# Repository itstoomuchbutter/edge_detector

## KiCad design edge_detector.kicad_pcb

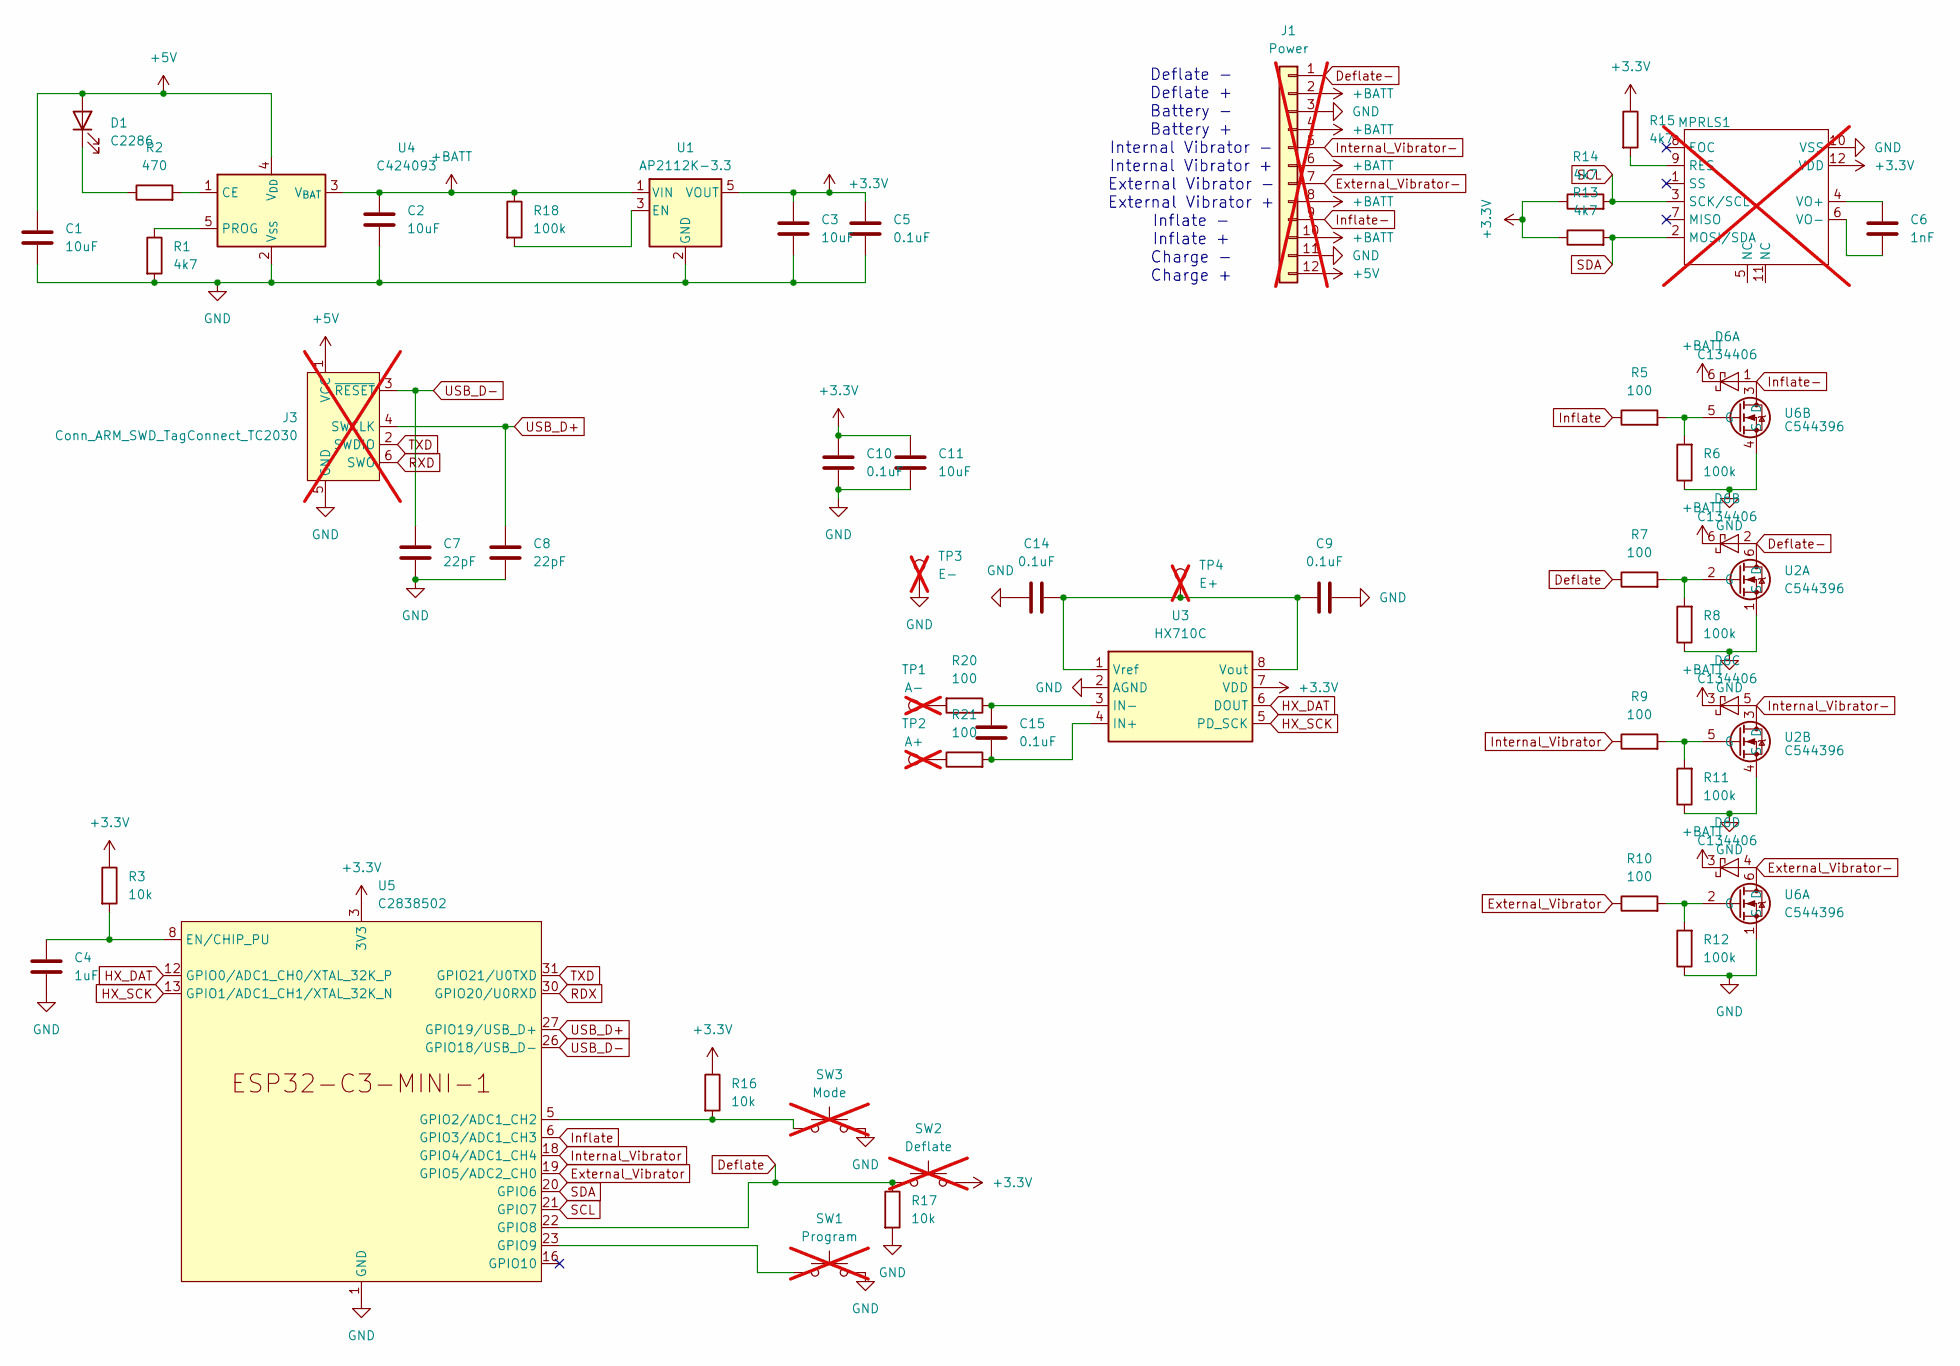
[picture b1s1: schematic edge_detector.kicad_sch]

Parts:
C1, C2, C3, C11: 10uF; C_0402_1005Metric; LCSC C15525
C4: 1uF; C_0402_1005Metric; LCSC C52923
C5, C9, C10, C14, C15: 0.1uF; C_0402_1005Metric; LCSC C1525
C6: 1nF; C_0402_1005Metric; LCSC C1523
C7, C8: 22pF; C_0402_1005Metric; LCSC C1555
D1: C2286; LED_0603_1608Metric; LCSC C2286
D6: C134406; SOT-363_SC-70-6; LCSC C134406
J1: Power; Molex_PicoBlade_53048-1210_1x12_P1.25mm_Horizontal; not fitted
J3: Conn_ARM_SWD_TagConnect_TC2030; Tag-Connect_TC2030-IDC-NL_2x03_P1.27mm_Vertical; not fitted
MPRLS1: MPRLS0015PA0000SA; not fitted
R1, R13, R14, R15: 4k7; R_0402_1005Metric; LCSC C25900
R2: 470; R_0402_1005Metric; LCSC C25117
R3, R16, R17: 10k; R_0402_1005Metric; LCSC C25744
R5, R7, R9, R10, R20, R21: 100; R_0402_1005Metric; LCSC C25076
R6, R8, R11, R12, R18: 100k; R_0402_1005Metric; LCSC C25741
SW1: Program; SW_SPST_PTS645; not fitted
SW2: Deflate; SW_SPST_PTS645; not fitted
SW3: Mode; SW_SPST_PTS645; not fitted
TP1: A-; TestPoint_Pad_1.0x1.0mm; not fitted
TP2: A+; TestPoint_Pad_1.0x1.0mm; not fitted
TP3: E-; TestPoint_Pad_1.0x1.0mm; not fitted
TP4: E+; TestPoint_Pad_1.0x1.0mm; not fitted
U1: AP2112K-3.3; SOT-23-5; LCSC C51118
U2, U6: C544396; WSON-6-1EP_2x2mm_P0.65mm_EP1x1.6mm; LCSC C544396
U3: HX710C; SOP-8_3.9x4.9mm_P1.27mm; LCSC C124156
U4: C424093; SOT-23-5; LCSC C424093
U5: C2838502; ESP32-C3-MINI-1; LCSC C2838502

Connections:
+3.3V: C3.1, C5.1, C10.1, C11.1, MPRLS1.12 (VDD), R3.1, R13.1, R14.1, R15.1, R16.1, SW2.2, U1.5 (VOUT), U3.7 (VDD), U5.3 (3V3)
+5V: C1.1, D1.2 (A), J1.12, J3.1 (VCC), U4.4 (V_{DD})
+BATT: C2.1, D6.3 (K), D6.6 (K), J1.2, J1.4, J1.6, J1.8, J1.10, R18.1, U1.1 (VIN), U4.3 (V_{BAT})
Deflate: R7.1, R17.1, SW2.1, U5.22 (GPIO8)
Deflate-: D6.2 (A), J1.1, U2.6 (D)
External_Vibrator: R10.1, U5.19 (GPIO5/ADC2_CH0)
External_Vibrator-: D6.4 (A), J1.7, U6.6 (D)
GND: C1.2, C2.2, C3.2, C4.2, C5.2, C7.2, C8.2, C9.2, C10.2, C11.2, C14.1, J1.3, J1.11, J3.5 (GND), MPRLS1.10 (VSS), R1.2, R6.1, R8.1, R11.1, R12.1, R17.2, SW1.2, SW3.2, TP3.1, U1.2 (GND), U2.1 (S), U2.4 (S), U3.2 (AGND), U4.2 (V_{SS}), U5.1 (GND), U5.2 (GND), U5.11 (GND), U5.14 (GND), U5.36 (GND), U5.37 (GND), U5.38 (GND), U5.39 (GND), U5.40 (GND), U5.41 (GND), U5.42 (GND), U5.43 (GND), U5.44 (GND), U5.45 (GND), U5.46 (GND), U5.47 (GND), U5.48 (GND), U5.49 (GND), U5.50 (GND), U5.51 (GND), U5.52 (GND), U5.53 (GND), U6.1 (S), U6.4 (S)
HX_DAT: U3.6 (DOUT), U5.12 (GPIO0/ADC1_CH0/XTAL_32K_P)
HX_SCK: U3.5 (PD_SCK), U5.13 (GPIO1/ADC1_CH1/XTAL_32K_N)
Inflate: R5.1, U5.6 (GPIO3/ADC1_CH3)
Inflate-: D6.1 (A), J1.9, U6.3 (D)
Internal_Vibrator: R9.1, U5.18 (GPIO4/ADC1_CH4)
Internal_Vibrator-: D6.5 (A), J1.5, U2.3 (D)
unnamed: D1.1 (K), R2.1
unnamed: MPRLS1.9 (RES), R15.2
unnamed: C6.1, MPRLS1.4 (VO+)
unnamed: C6.2, MPRLS1.6 (VO-)
unnamed: R20.2, TP1.1
unnamed: R21.1, TP2.1
unnamed: R18.2, U1.3 (EN)
unnamed: R7.2, R8.2, U2.2 (G)
unnamed: R9.2, R11.2, U2.5 (G)
unnamed: C15.2, R21.2, U3.4 (IN+)
unnamed: C15.1, R20.1, U3.3 (IN-)
unnamed: C9.1, C14.2, TP4.1, U3.1 (Vref), U3.8 (Vout)
unnamed: R2.2, U4.1 (CE)
unnamed: R1.1, U4.5 (PROG)
unnamed: C4.1, R3.2, U5.8 (EN/CHIP_PU)
unnamed: R16.2, SW3.1, U5.5 (GPIO2/ADC1_CH2)
unnamed: SW1.1, U5.23 (GPIO9)
unnamed: R10.2, R12.2, U6.2 (G)
unnamed: R5.2, R6.2, U6.5 (G)
RDX: U5.30 (GPIO20/U0RXD)
RXD: J3.6 (SWO)
SCL: MPRLS1.3 (SCK/SCL), R14.2, U5.21 (GPIO7)
SDA: MPRLS1.2 (MOSI/SDA), R13.2, U5.20 (GPIO6)
TXD: J3.2 (SWDIO), U5.31 (GPIO21/U0TXD)
USB_D+: C8.1, J3.4 (SWCLK), U5.27 (GPIO19/USB_D+)
USB_D-: C7.1, J3.3 (~RESET), U5.26 (GPIO18/USB_D-)

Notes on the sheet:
Deflate - Deflate + Battery - Battery + Internal Vibrator - Internal Vibrator + External Vibrator - External Vibrator + Inflate - Inflate + Charge - Charge +

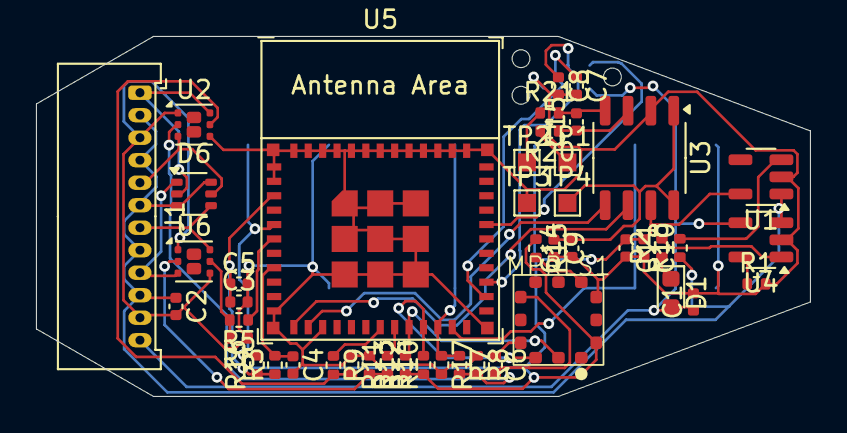
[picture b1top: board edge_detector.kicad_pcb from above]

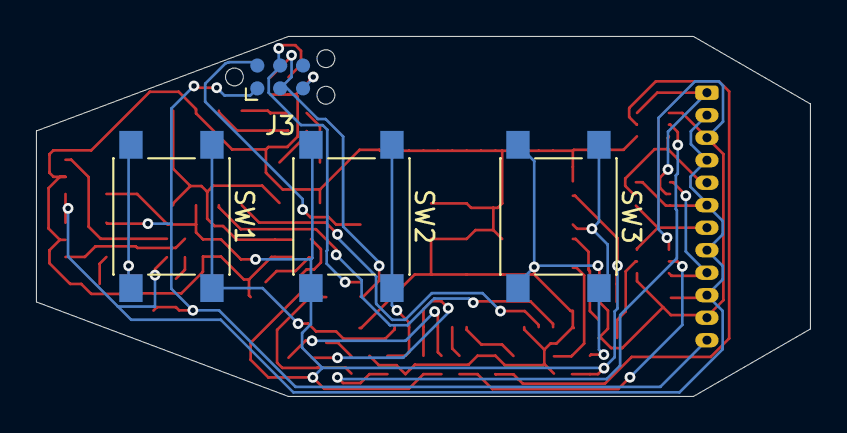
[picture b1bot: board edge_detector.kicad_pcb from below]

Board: 2 copper layers, 43.0 x 20.0 mm, 50 parts (4 on the bottom side), 38 nets.

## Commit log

2024-04-04 Preparing second order
